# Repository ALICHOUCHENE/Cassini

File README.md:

# Cassini

Autonomous robot based on STM32f407

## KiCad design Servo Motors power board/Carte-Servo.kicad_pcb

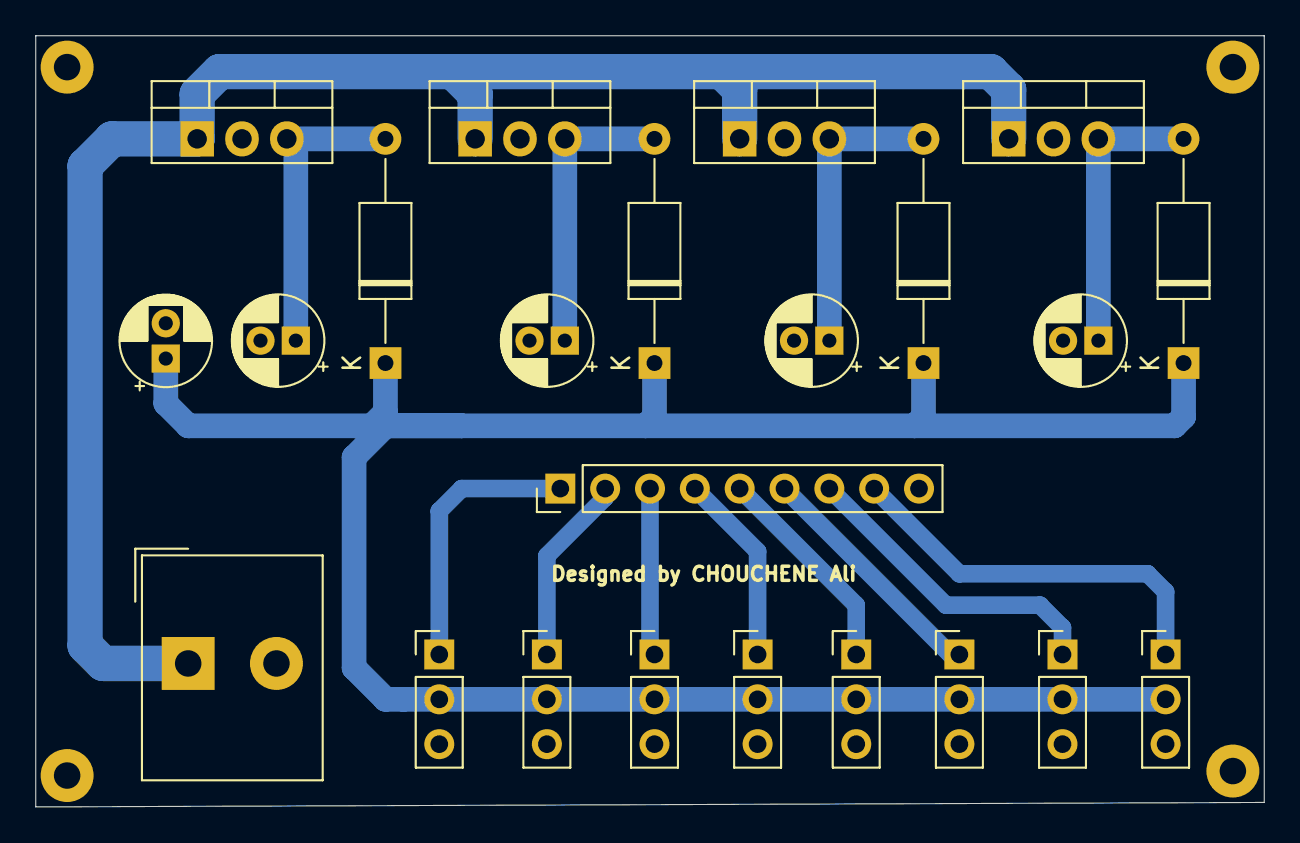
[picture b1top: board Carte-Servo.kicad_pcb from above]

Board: 2 copper layers, 69.6 x 43.7 mm, 27 parts (0 on the bottom side), 15 nets.

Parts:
C2, C3, C4, C5: 100nF; CP_Radial_D5.0mm_P2.00mm
Ce: 100nF; CP_Radial_D5.0mm_P2.00mm
D1, D2, D3, D4: D_Schottky; D_A-405_P12.70mm_Horizontal
H1, H2, H3, H4: MountingHole_Pad; MountingHole_2.5mm_Pad
J1: Input Voltage (Up to 36V); Altech_AK300_1x02_P5.00mm_45-Degree
J2: Servo1; PinHeader_1x03_P2.54mm_Vertical
J3: Servo2; PinHeader_1x03_P2.54mm_Vertical
J4: Servo3; PinHeader_1x03_P2.54mm_Vertical
J5: Servo4; PinHeader_1x03_P2.54mm_Vertical
J6: Servo5; PinHeader_1x03_P2.54mm_Vertical
J7: Servo6; PinHeader_1x03_P2.54mm_Vertical
J8: Servo7; PinHeader_1x03_P2.54mm_Vertical
J9: Servo8; PinHeader_1x03_P2.54mm_Vertical
J10: PWM signal from MCU; PinHeader_1x09_P2.54mm_Vertical
U1, U2, U3, U4: L7805; TO-220-3_Vertical

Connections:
+5V: C5.1, D1.1, D2.1, D3.1, D4.1, J2.2, J3.2, J4.2, J5.2, J6.2, J7.2, J8.2, J9.2
+12V: J1.1, U1.1, U2.1, U3.1, U4.1
GND: C2.2, C3.2, C4.2, C5.2, Ce.2, H1.1, H2.1, H3.1, H4.1, J1.2, J2.3, J3.3, J4.3, J5.3, J6.3, J7.3, J8.3, J9.3, J10.9, U1.2, U2.2, U3.2, U4.2
unnamed: Ce.1, D1.2, U1.3
unnamed: C2.1, D2.2, U2.3
unnamed: C3.1, D3.2, U3.3
unnamed: C4.1, D4.2, U4.3
PWM1: J2.1, J10.1
PWM2: J3.1, J10.2
PWM3: J4.1, J10.3
PWM4: J5.1, J10.4
PWM5: J6.1, J10.5
PWM6: J7.1, J10.6
PWM7: J8.1, J10.7
PWM8: J9.1, J10.8

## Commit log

2021-04-22 Create ST
